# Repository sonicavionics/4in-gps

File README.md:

# GPS Module Repository

---

<div align="center">
  <div>

    <p><em>3D Render</em></p>
  </div>
  <br>

  <div>
    <br>
    <p><em>Schematic</em></p>
  </div>
  <br>
  
  <div>
    
    <br>
    <em>Footprint</em>
  </div>
</div>

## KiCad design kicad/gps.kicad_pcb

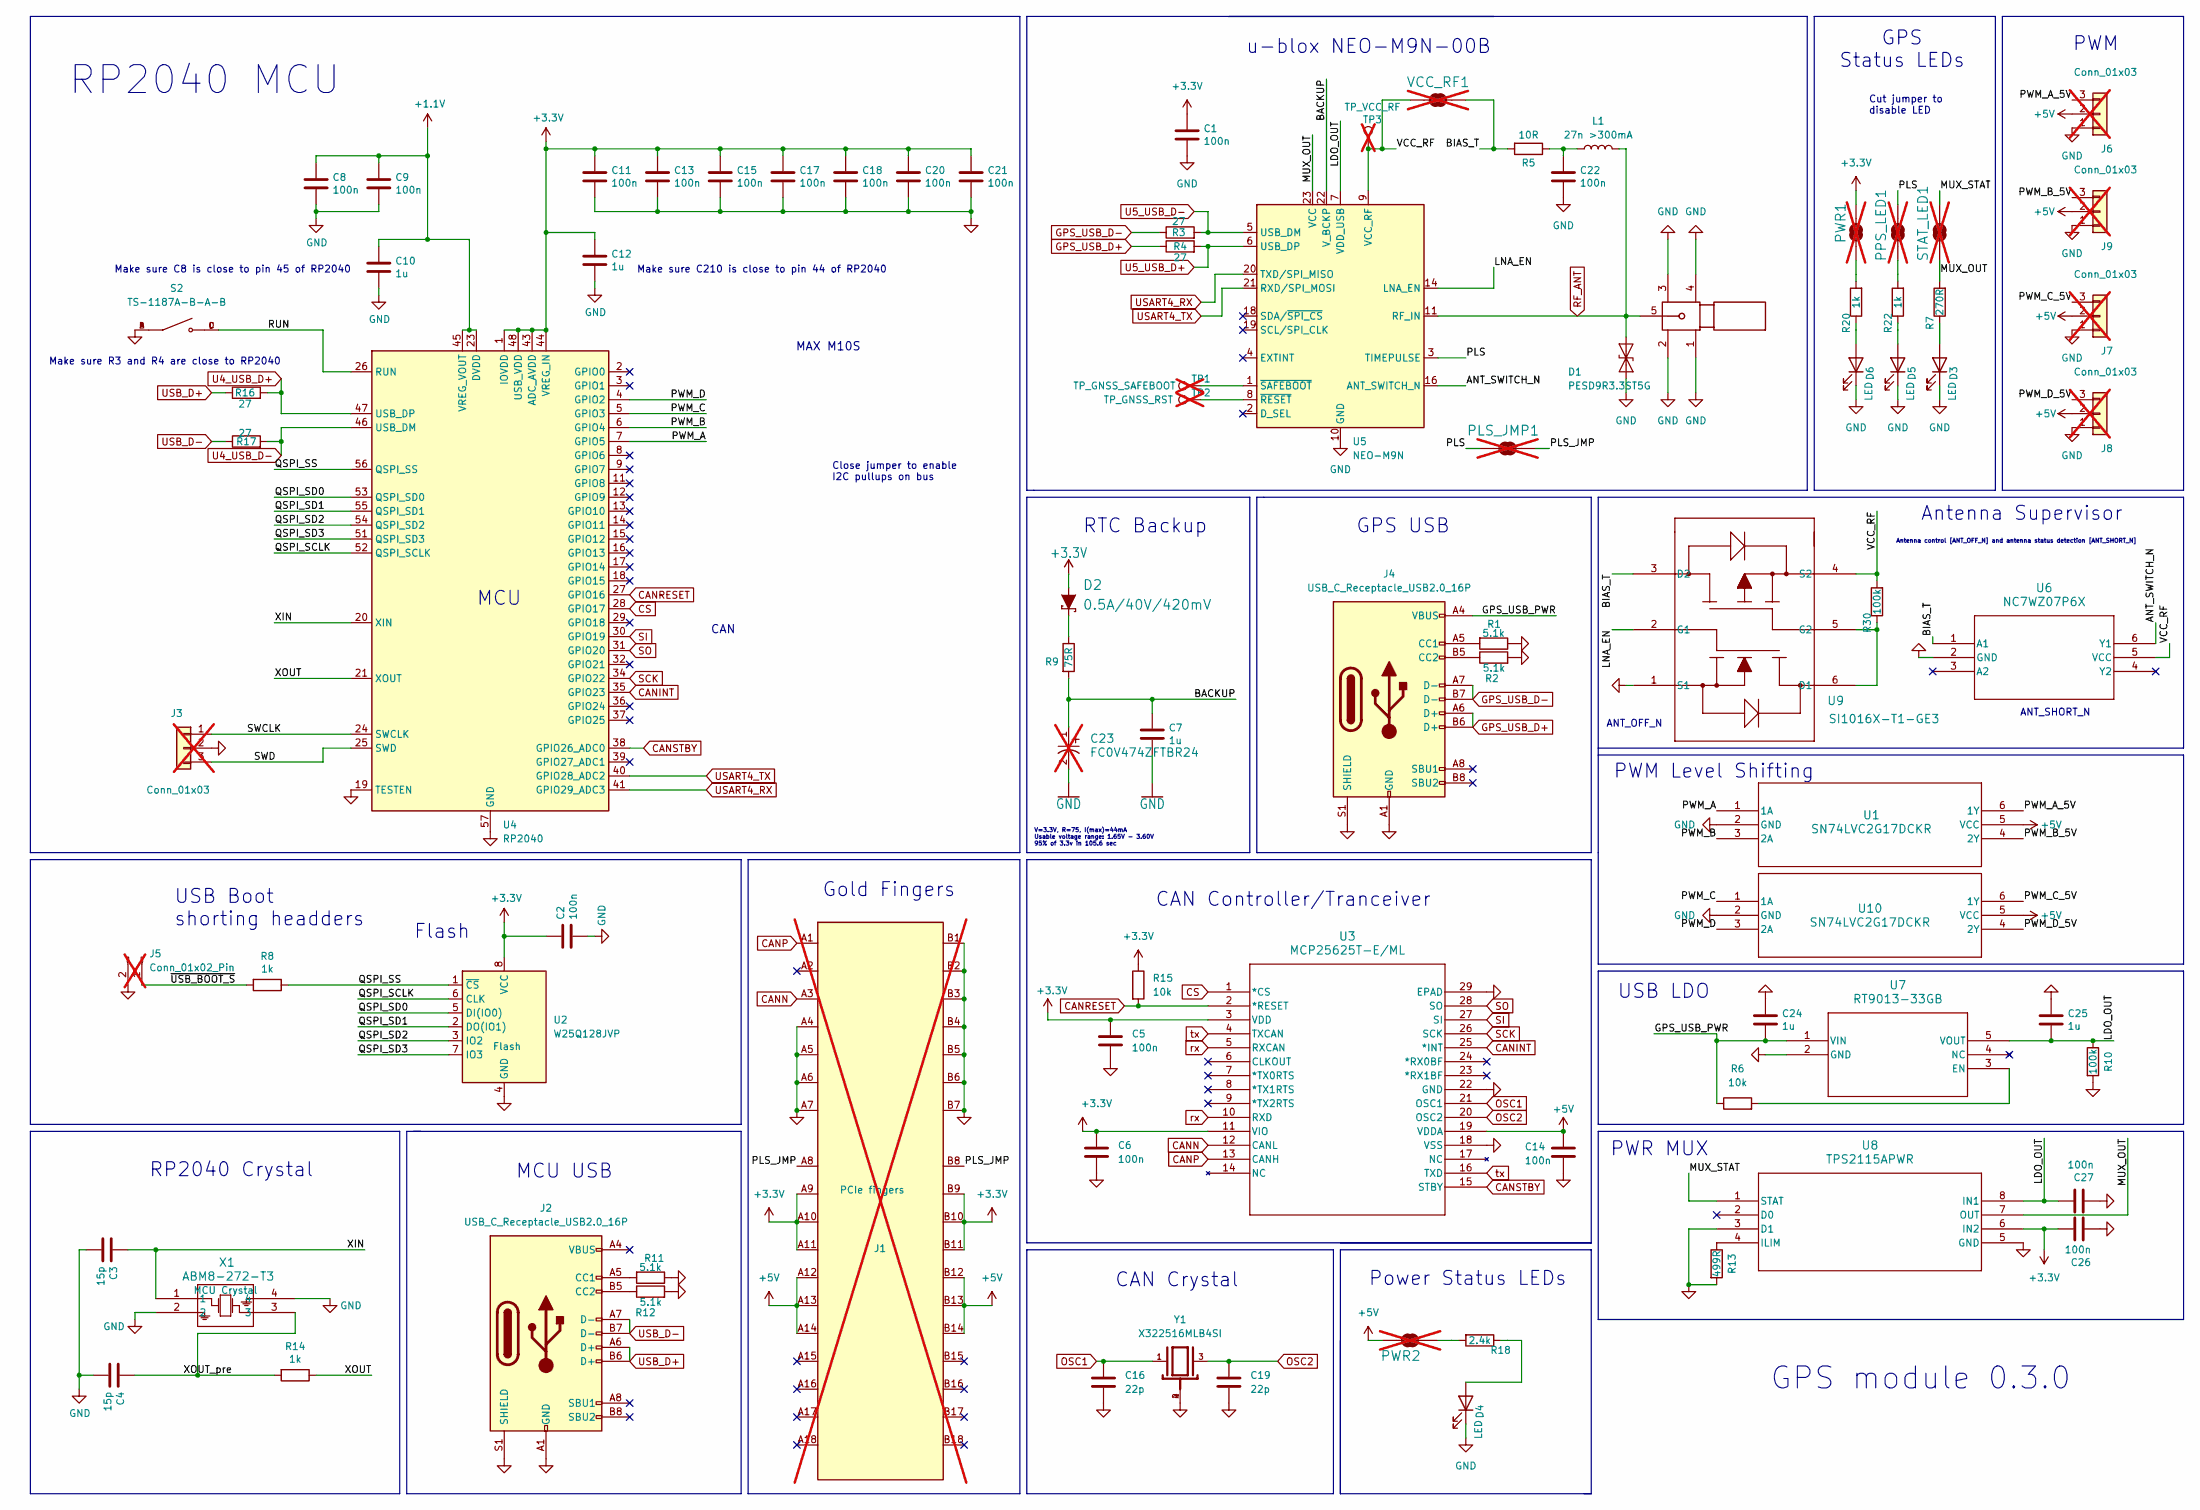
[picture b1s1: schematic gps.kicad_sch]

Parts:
C1, C2, C5, C6, C8, C9, C11, C13, C14, C15, C17, C18, C20, C21, C22, C26, C27: 100n; C_0402_1005Metric; LCSC Part # C307331
C3, C4: 15p; C_0402_1005Metric; LCSC Part # C1548
C7, C10, C12, C24, C25: 1u; C_0402_1005Metric; LCSC Part # C52923
C16, C19: 22p; C_0402_1005Metric; LCSC Part # C1555
C23: FC0V474ZFTBR24; FC0V474ZFTBR24_KEM; not fitted
D1: PESD9R3.3ST5G; D_SOD-923; LCSC C2912536
D2: 0.5A/40V/420mV; SOD-323; Manufacturer Part Number PMEGA4005EJ,115; LCSC Part # C426868
D3: LED; LED_0603_1608Metric; Manufacturer_Part_Number XL-1608UWC-04; LCSC Part # C965808
D4: LED; LED_0603_1608Metric; LCSC Part # C2286
D5: LED; LED_0603_1608Metric; Manufacturer_Part_Number KT-0603B; LCSC Part # C2288
D6: LED; LED_0603_1608Metric; Manufacturer_Part_Number KT-0603R; LCSC Part # C2286
J1: Bus_PCI_Express_x1; BUS_PCIexpress_x1; LCSC Part # n/a; not fitted
J2, J4: USB_C_Receptacle_USB2.0_16P; USB_C_Receptacle_Palconn_UTC16-G; LCSC Part # C2765186
J3: Conn_01x03; DEBUGHEADER; LCSC Part # n/a; not fitted
J5: Conn_01x02_Pin; SolderJumper-2_P1.3mm_Open_RoundedPad1.0x1.5mm; not fitted
J6, J7, J8, J9: Conn_01x03; PinHeader_1x03_P2.54mm_Vertical; LCSC Part # n/a; not fitted
L1: 27n >300mA; R_0402_1005Metric; Manufacturer Part Number LQG15HS27NJ02D; LCSC Part # C12669
PLS_JMP1: JUMPER-SMT_2_NC_TRACE_SILK; SolderJumper-2_P1.3mm_Open_RoundedPad1.0x1.5mm; not fitted
PPS_LED1: JUMPER-SMT_2_NC_TRACE_SILK; SMT-JUMPER_2_NC_TRACE_SILK; not fitted
PWR1, PWR2: JUMPER-SMT_2_NC_TRACE_SILK; SMT-JUMPER_2_NC_TRACE_SILK; not fitted
R1, R2, R11, R12: 5.1k; R_0402_1005Metric; LCSC Part # C25905
R3, R4, R16, R17: 27; R_0402_1005Metric; LCSC Part # C25100
R5: 10R; R_0402_1005Metric; Manufacturer Part Number 0402WGF100JTCE; LCSC Part # C25077
R6, R15: 10k; R_0402_1005Metric; LCSC Part # C25744
R7: 270R; R_0402_1005Metric; Manufacturer_Part_Number 0402WGF2700TCE; LCSC Part # C25099
R8, R14, R20, R22: 1k; R_0402_1005Metric; LCSC Part # C11702
R9: 75R; R_0805_2012Metric; Manufacturer_Part_Number 0805W8F750JT5E; LCSC Part # C17820
R10, R30: 100k; R_0402_1005Metric; Manufacturer Part Number 0402WGF1003TCE; LCSC Part # C25741
R13: 499R; R_0402_1005Metric; Manufacturer Part Number 0402WGF4990TCE; LCSC Part # C4125
R18: 2.4k; R_0402_1005Metric; Manufacturer_Part_Number 0402WGF2401TCE; LCSC Part # C25882
RF1: BWSMA-KWE-Z001; SMA-TH_BWSMA-KWE-Z001; Manufacturer Part Number BWSMA-KWE-Z001; LCSC Part # C496551
S2: TS-1187A-B-A-B; SW_TS-1187A-B-A-B; PARTREV A0; LCSC Part # C318884
STAT_LED1: JUMPER-SMT_2_NC_TRACE_SILK; SMT-JUMPER_2_NC_TRACE_SILK; not fitted
TP1: TP_GNSS_SAFEBOOT; TestPoint_Pad_D1.0mm; not fitted
TP2: TP_GNSS_RST; TestPoint_Pad_D1.0mm; not fitted
TP3: TP_VCC_RF; TestPoint_Pad_D1.0mm; not fitted
U1, U10: SN74LVC2G17DCKR; DCK6; MFR.Part # SN74LVC2G17DCKR; JLC Link JLCPCB Part
U2: W25Q128JVP; WSON-8-1EP_6x5mm_P1.27mm_EP3.4x4.3mm; LCSC C190862
U3: MCP25625T-E/ML; QFN28_6X6MC_MCH; LCSC Part # C191253
U4: RP2040; QFN-56-1EP_7x7mm_P0.4mm_EP3.2x3.2mm; LCSC C2040
U5: NEO-M9N; ublox_NEO
U6: NC7WZ07P6X; SC-88&slash_SC70-6&slash_SOT-363_419B-02_ONS; MFR.Part # NC7WZ07P6X; LCSC Part # C95342
U7: RT9013-33GB; SOT-23-5_RIT_LDO; MFR.Part # RT9013-33GB; LCSC Part # C47773
U8: TPS2115APWR; PW8
U9: SI1016X-T1-GE3; SOT_X-T1-GE3_VIS; Manufacturer Part Number SI1016X-T1-GE3; LCSC Part # C142570
VCC_RF1: JUMPER-SMT_2_NC_TRACE_SILK; SMT-JUMPER_2; not fitted
X1: ABM8-272-T3; ABM8-272-T3_ABR; LCSC Part # C20625731
Y1: X322516MLB4SI; OSC_X322516MLB4SI; PARTREV N/A; LCSC Part # C12668

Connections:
+1.1V: C8.1, C9.1, C10.1, U4.23 (DVDD), U4.45 (VREG_VOUT), U4.50 (DVDD)
+3.3V: C1.1, C2.1, C5.1, C6.1, C11.1, C12.1, C13.1, C15.1, C17.1, C18.1, C20.1, C21.1, C26.1, D2.A, J1.A9 (+3.3V), J1.A10 (+3.3V), J1.A11 (~PERST), J1.B9 (JTAG1), J1.B10 (3.3Vaux), J1.B11 (~WAKE), PWR1.2, R15.1, U2.8 (VCC), U3.3 (VDD), U3.11 (VIO), U4.1 (IOVDD), U4.10 (IOVDD), U4.22 (IOVDD), U4.33 (IOVDD), U4.42 (IOVDD), U4.43 (ADC_AVDD), U4.44 (VREG_IN), U4.48 (USB_VDD), U4.49 (IOVDD), U8.6 (IN2)
+5V: C14.1, J1.A12 (GND), J1.A13 (REFCLK+), J1.A14 (REFCLK-), J1.B12 (RSVD), J1.B13 (GND), J1.B14 (PETp0), J6.2, J7.2, J8.2, J9.2, PWR2.2, U1.5 (VCC), U3.19 (VDDA), U10.5 (VCC)
/ANT_SWITCH_N: U5.16 (ANT_SWITCH_N), U6.6 (Y1)
/BACKUP: C7.1, C23.1, R9.2, U5.22 (V_BCKP)
/BIAS_T: R5.2, U6.1 (A1), U9.3 (D2), VCC_RF1.1
/GPS_USB_PWR: C24.2, J4.A4 (VBUS), J4.A9 (VBUS), J4.B4 (VBUS), J4.B9 (VBUS), R6.1, U7.1 (VIN)
/LDO_OUT: C25.2, C27.1, R10.1, U5.7 (VDD_USB), U7.5 (VOUT), U8.8 (IN1)
/LNA_EN: U5.14 (LNA_EN), U9.2 (G1)
/MUX_OUT: R7.2, STAT_LED1.1, U5.23 (VCC), U8.7 (OUT)
/MUX_STAT: STAT_LED1.2, U8.1 (STAT)
/PLS: PLS_JMP1.2, PPS_LED1.2, U5.3 (TIMEPULSE); also elsewhere on the board
/PLS_JMP: J1.A8 (JTAG5), J1.B8 (+3.3V), PLS_JMP1.1; also elsewhere on the board
/PWM_A: U1.1 (1A), U4.7 (GPIO5)
/PWM_A_5V: J6.3, U1.6 (1Y)
/PWM_B: U1.3 (2A), U4.6 (GPIO4)
/PWM_B_5V: J9.3, U1.4 (2Y)
/PWM_C: U4.5 (GPIO3), U10.1 (1A)
/PWM_C_5V: J7.3, U10.6 (1Y)
/PWM_D: U4.4 (GPIO2), U10.3 (2A)
/PWM_D_5V: J8.3, U10.4 (2Y)
/QSPI_SCLK: U2.6 (CLK), U4.52 (QSPI_SCLK)
/QSPI_SD0: U2.5 (DI(IO0)), U4.53 (QSPI_SD0)
/QSPI_SD1: U2.2 (DO(IO1)), U4.55 (QSPI_SD1)
/QSPI_SD2: U2.3 (IO2), U4.54 (QSPI_SD2)
/QSPI_SD3: U2.7 (IO3), U4.51 (QSPI_SD3)
/QSPI_SS: R8.1, U2.1 (~CS), U4.56 (QSPI_SS)
/RUN: S2.C, S2.D, U4.26 (RUN)
/SWCLK: J3.1, U4.24 (SWCLK)
/SWD: J3.3, U4.25 (SWD)
/VCC_RF: R30.2, TP3.1, U5.9 (VCC_RF), U6.5 (VCC), U9.4 (S2), VCC_RF1.2
/XIN: C3.1, U4.20 (XIN), X1.1
/XOUT: R14.1, U4.21 (XOUT)
/XOUT_pre: C4.1, R14.2, X1.3
/~USB_BOOT_S: J5.1, R8.2
CANINT: U3.25 (*INT), U4.35 (GPIO23)
CANN: J1.A3 (+12V), U3.12 (CANL)
CANP: J1.A1 (~PRSNT1), U3.13 (CANH)
CANRESET: R15.2, U3.2 (*RESET), U4.27 (GPIO16)
CANSTBY: U3.15 (STBY), U4.38 (GPIO26_ADC0)
CS: U3.1 (*CS), U4.28 (GPIO17)
GND: C1.2, C2.2, C3.2, C4.2, C5.2, C6.2, C7.2, C8.2, C9.2, C10.2, C11.2, C12.2, C13.2, C14.2, C15.2, C16.2, C17.2, C18.2, C19.2, C20.2, C21.2, C22.2, C23.2, C24.1, C25.1, C26.2, C27.2, D1.1 (A1), D3.1 (K), D4.1 (K), D5.1 (K), D6.1 (K), J1.A4 (GND), J1.A5 (JTAG2), J1.A6 (JTAG3), J1.A7 (JTAG4), J1.B1 (+12V), J1.B2 (+12V), J1.B3 (+12V), J1.B4 (GND), J1.B5 (SMCLK), J1.B6 (SMDAT), J1.B7 (GND), J2.A1 (GND), J2.A12 (GND), J2.B1 (GND), J2.B12 (GND), J2.S1 (SHIELD), J3.2, J4.A1 (GND), J4.A12 (GND), J4.B1 (GND), J4.B12 (GND), J4.S1 (SHIELD), J5.2, J6.1, J7.1, J8.1, J9.1, R1.1, R2.2, R10.2, R11.1, R12.2, R13.2, RF1.1, RF1.2, RF1.3, RF1.4, S2.A, S2.B, U1.2 (GND), U2.4 (GND), U3.18 (VSS), U3.22 (GND), U3.29 (EPAD), U4.19 (TESTEN), U4.57 (GND), U5.10 (GND), U5.12 (GND), U5.13 (GND), U5.24 (GND), U6.2 (GND), U7.2 (GND), U8.3 (D1), U8.5 (GND), U9.1 (S1), U10.2 (GND), X1.2, X1.4, Y1.2, Y1.4
GPS_USB_D+: J4.A6 (D+), J4.B6 (D+), R4.1
GPS_USB_D-: J4.A7 (D-), J4.B7 (D-), R3.1
unnamed: C22.1, L1.1, R5.1
unnamed: D2.C, R9.1
unnamed: D3.2 (A), R7.1
unnamed: D4.2 (A), R18.1
unnamed: D5.2 (A), R22.1
unnamed: D6.2 (A), R20.1
unnamed: J2.A5 (CC1), R11.2
unnamed: J2.B5 (CC2), R12.1
unnamed: J4.A5 (CC1), R1.2
unnamed: J4.B5 (CC2), R2.1
unnamed: PPS_LED1.1, R22.2
unnamed: PWR1.1, R20.2
unnamed: PWR2.1, R18.2
unnamed: TP2.1, U5.8 (~RESET)
unnamed: TP1.1, U5.1 (~SAFEBOOT)
unnamed: R6.2, U7.3 (EN)
unnamed: R13.1, U8.4 (ILIM)
unnamed: R30.1, U9.5 (G2), U9.6 (D1)
OSC1: C16.1, U3.21 (OSC1), Y1.1
OSC2: C19.1, U3.20 (OSC2), Y1.3
RF_ANT: D1.2 (A2), L1.2, RF1.5, U5.11 (RF_IN)
SCK: U3.26 (SCK), U4.34 (GPIO22)
SI: U3.27 (SI), U4.30 (GPIO19)
SO: U3.28 (SO), U4.31 (GPIO20)
U4_USB_D+: R16.2, U4.47 (USB_DP)
U4_USB_D-: R17.2, U4.46 (USB_DM)
U5_USB_D+: R4.2, U5.6 (USB_DP)
U5_USB_D-: R3.2, U5.5 (USB_DM)
USART4_RX: U4.41 (GPIO29_ADC3), U5.20 (TXD/SPI_MISO)
USART4_TX: U4.40 (GPIO28_ADC2), U5.21 (RXD/SPI_MOSI)
USB_D+: J2.A6 (D+), J2.B6 (D+), R16.1
USB_D-: J2.A7 (D-), J2.B7 (D-), R17.1
rx: U3.5 (RXCAN), U3.10 (RXD)
tx: U3.4 (TXCAN), U3.16 (TXD)

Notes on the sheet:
Flash
CAN Crystal
GPS Status LEDs
CAN Controller/Tranceiver
Make sure R3 and R4 are close to RP2040
ANT_OFF_N
RP2040 MCU
Gold Fingers
GPS module 0.3.0
USB Boot shorting headders
u-blox NEO-M9N-00B
GPS USB
MCU
Antenna Supervisor
RTC Backup
PWM Level Shifting
Make sure C210 is close to pin 44 of RP2040
MAX M10S
MCU USB
Power Status LEDs
USB LDO
Cut jumper to disable LED
PWR MUX
ANT_SHORT_N
V=3.3V, R=75, I(max)=44mA Usable voltage range: 1.65V - 3.60V 95% of 3.3v in 105.6 sec
RP2040 Crystal
Antenna control [ANT_OFF_N] and antenna status detection [ANT_SHORT_N]
CAN
Make sure C8 is close to pin 45 of RP2040
Close jumper to enable I2C pullups on bus
PWM

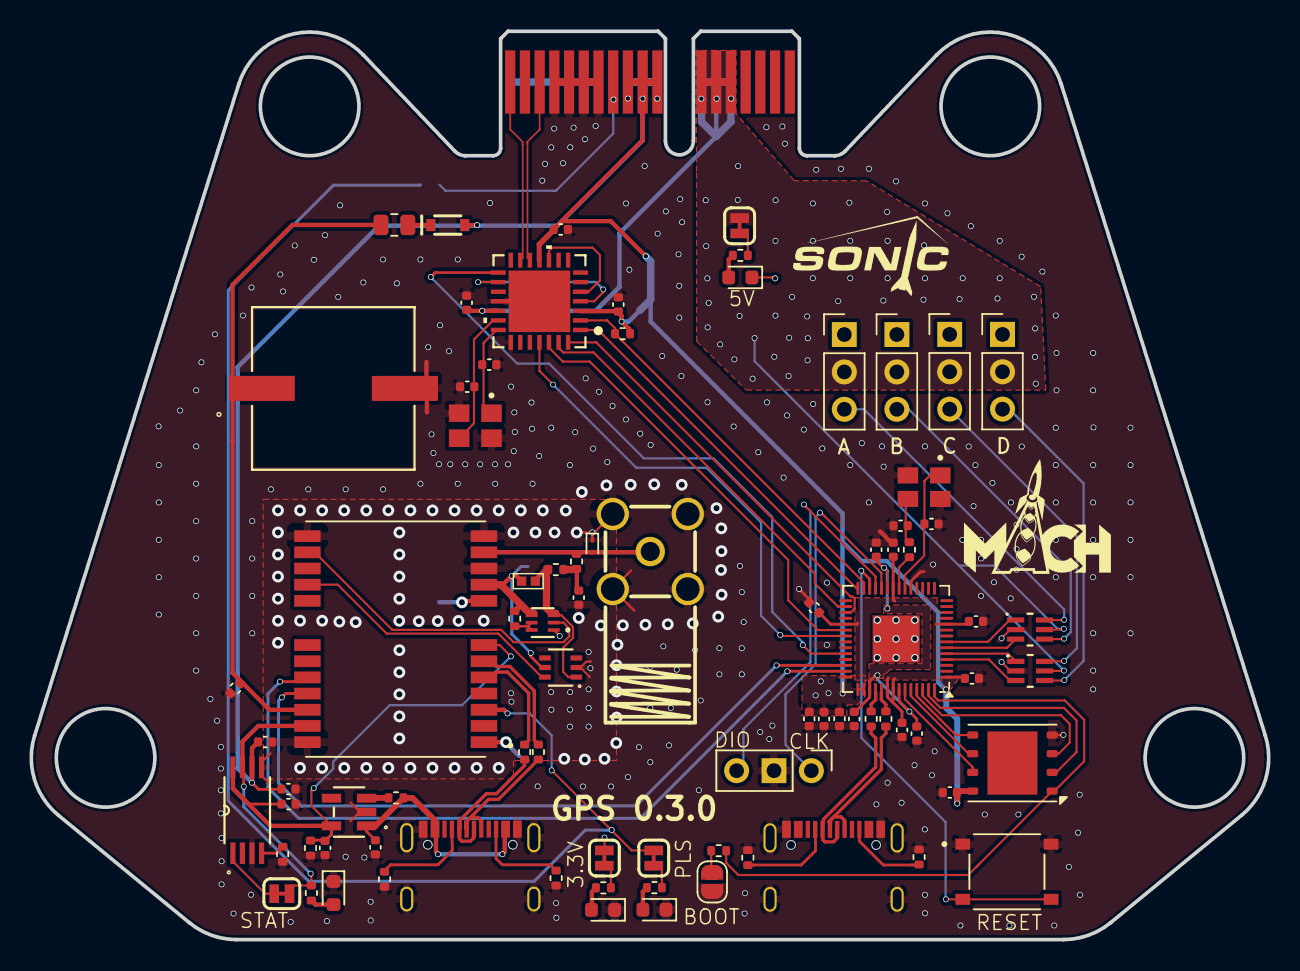
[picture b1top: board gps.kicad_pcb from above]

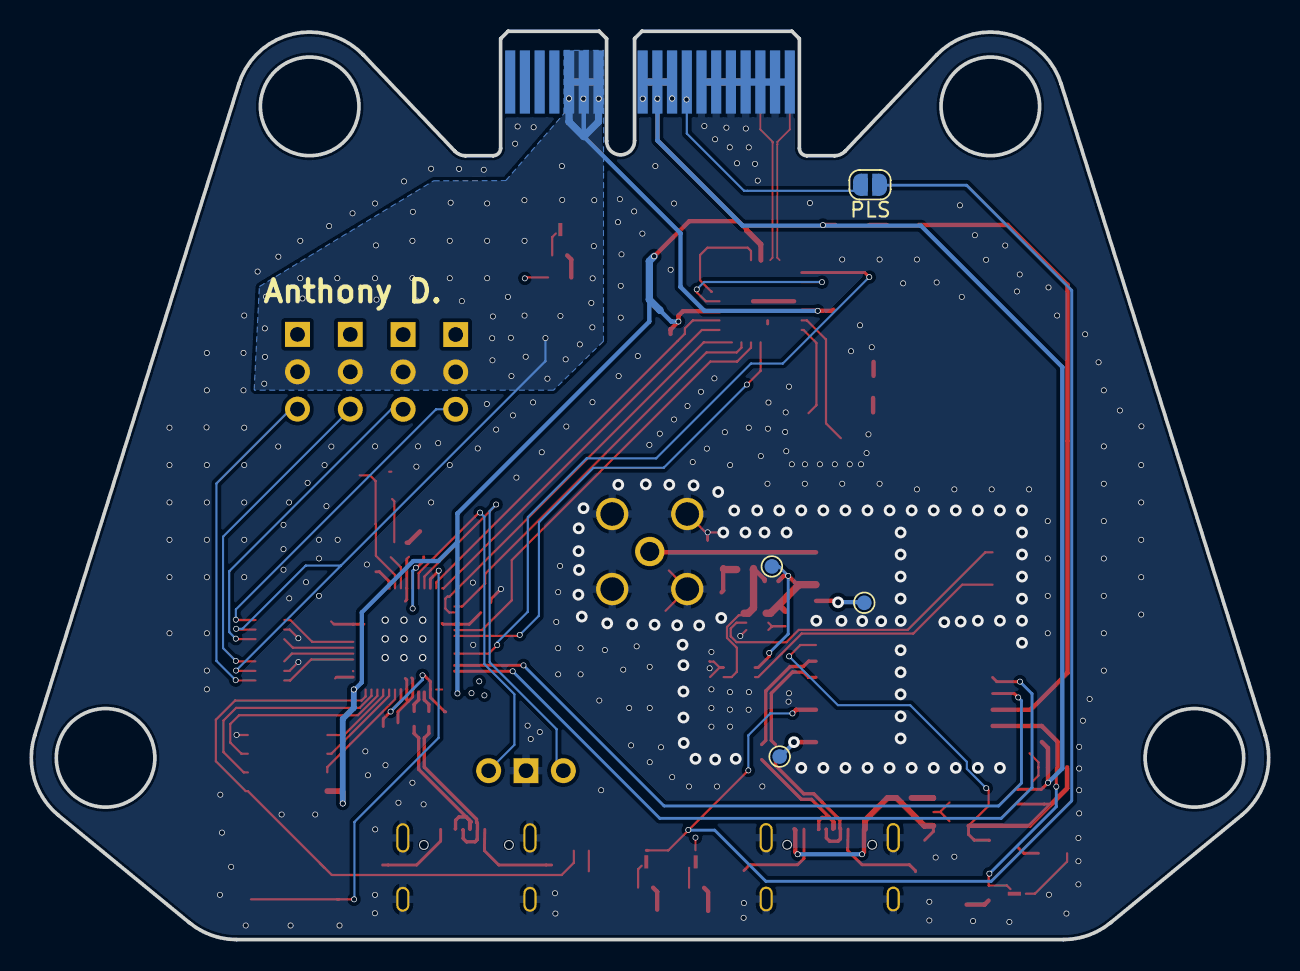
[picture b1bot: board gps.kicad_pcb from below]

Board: 4 copper layers, 84.1 x 61.7 mm, 88 parts (5 on the bottom side), 78 nets.

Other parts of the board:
PLS: JUMPER-SMT_2_NC_TRACE_SILK; SolderJumper-2_P1.3mm_Open_RoundedPad1.0x1.5mm
ballsack1: a5b3f77c-c1d0-4586-9ab7-7f2af37e3489

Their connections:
/PLS: PLS.2; also elsewhere on the board
/PLS_JMP: PLS.1; also elsewhere on the board

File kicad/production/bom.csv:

Designator,Footprint,Quantity,Value,LCSC Part #
BALLSACK1,a5b3f77c-c1d0-4586-9ab7-7f2af37e3489,1,,
"C1, C11, C13, C14, C15, C17, C18, C2, C20, C21, C22, C26, C27, C5, C6, C8, C9",0402,17,100n,C307331
"C10, C12, C24, C25, C7",0402,5,1u,C52923
"C16, C19",0402,2,22p,C1555
"C3, C4",0402,2,15p,C1548
D1,D_SOD-923,1,PESD9R3.3ST5G,C2912536
D2,SOD-323,1,0.5A/40V/420mV,C426868
D3,0603,1,LED,C965808
"D4, D6",0603,2,LED,C2286
D5,0603,1,LED,C2288
"J2, J4",USB_C_Receptacle_Palconn_UTC16-G,2,USB_C_Receptacle_USB2.0_16P,C2765186
L1,0402,1,27n >300mA,C12669
"R1, R11, R12, R2",0402,4,5.1k,C25905
"R10, R30",0402,2,100k,C25741
R13,0402,1,499R,C4125
"R14, R20, R22, R8",0402,4,1k,C11702
"R15, R6",0402,2,10k,C25744
"R16, R17, R3, R4",0402,4,27,C25100
R18,0402,1,2.4k,C25882
R5,0402,1,10R,C25077
R7,0402,1,270R,C25099
R9,0805,1,75R,C17820
RF1,SMA-TH_BWSMA-KWE-Z001,1,BWSMA-KWE-Z001,C496551
S2,SW_TS-1187A-B-A-B,1,TS-1187A-B-A-B,C318884
"U1, U10",DCK6,2,SN74LVC2G17DCKR,C50714
U2,WSON-8-1EP_6x5mm_P1.27mm_EP3.4x4.3mm,1,W25Q128JVP,C190862
U3,QFN28_6X6MC_MCH,1,MCP25625T-E/ML,C191253
U4,QFN-56-1EP_7x7mm_P0.4mm_EP3.2x3.2mm,1,RP2040,C2040
U5,XCVR_NEO-M9N-00B,1,NEO-M9N,
U6,SC-88&slash_SC70-6&slash_SOT-363_419B-02_ONS,1,NC7WZ07P6X,C95342
U7,SOT-23-5_RIT_LDO,1,RT9013-33GB,C47773
U8,PW8,1,TPS2115APWR,
U9,SOT_X-T1-GE3_VIS,1,SI1016X-T1-GE3,C142570
X1,ABM8-272-T3_ABR,1,ABM8-272-T3,C20625731
Y1,OSC_X322516MLB4SI,1,X322516MLB4SI,C12668

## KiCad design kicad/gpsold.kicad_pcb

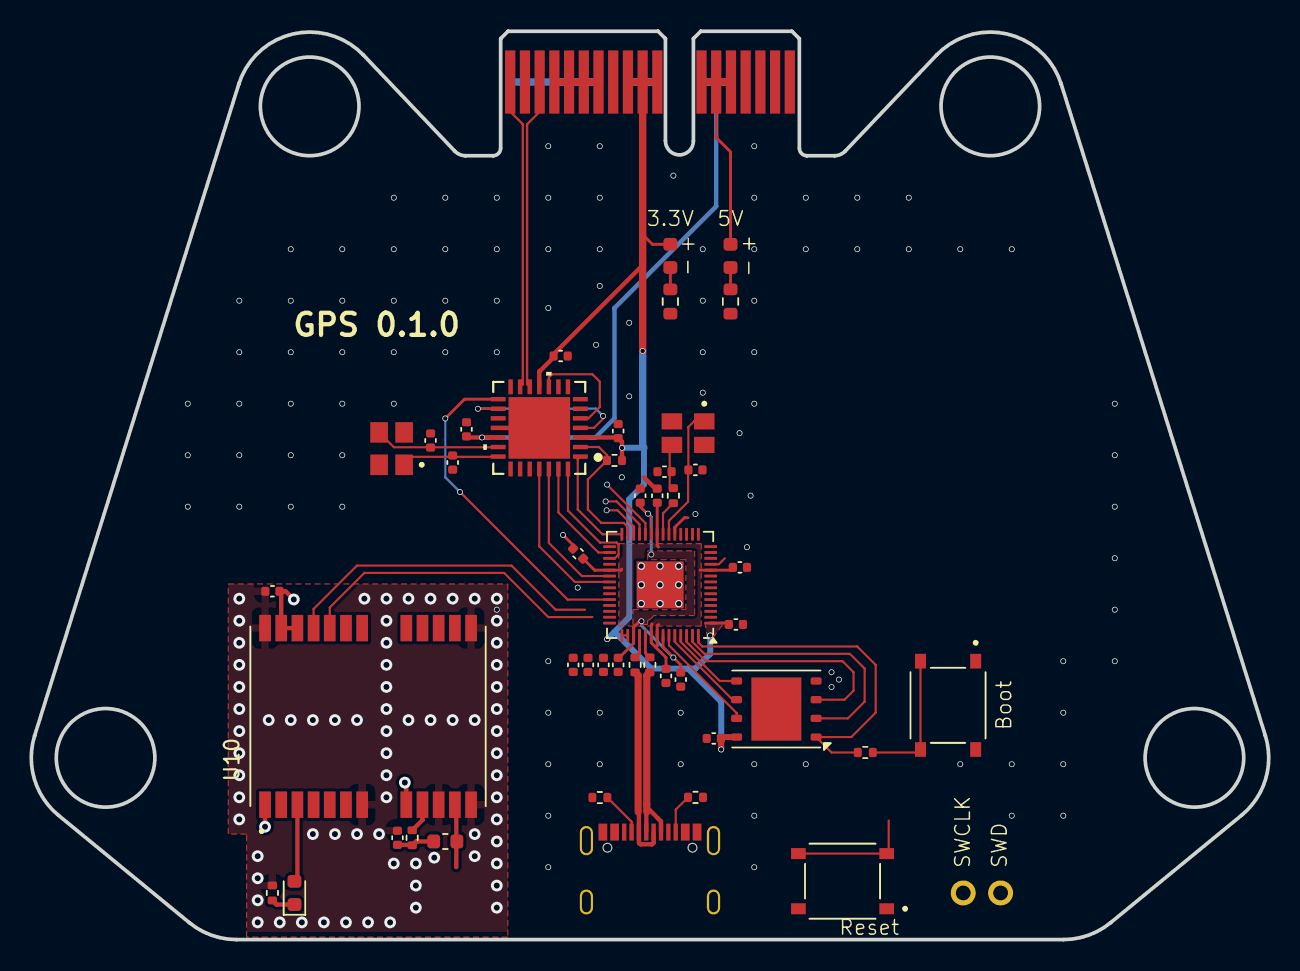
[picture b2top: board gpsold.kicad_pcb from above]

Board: 2 copper layers, 84.1 x 61.7 mm, 47 parts (1 on the bottom side), 38 nets.

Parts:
C10, C11: 15p; C_0402_1005Metric
C32: 100n 10% 16V X7R; C_0402_1005Metric
C33, C40, C90, C92, C93, C206, C207, C209, C211, C212, C213, C214, C215, C216: 100n; C_0402_1005Metric
C94, C95: 22p; C_0402_1005Metric
C208, C210: 1u; C_0402_1005Metric
D1, D2: LED; LED_0603_1608Metric
D2#2: BLUE; LED_0603_1608Metric
J1: Bus_PCI_Express_x1; BUS_PCIexpress_x1
J4: Conn_01x02; PinHeader_1x02_P2.54mm_Vertical
J6: USB_C_Receptacle_USB2.0_16P; USB_C_Receptacle_Palconn_UTC16-G
L5: 27n >300mA; L_0603_1608Metric
R1, R2: 150; R_0603_1608Metric
R3: 10R; R_0402_1005Metric
R3#2, R4#2: 5.1k; R_0402_1005Metric
R4, R12, R30: 1k; R_0402_1005Metric
R91: 10k; R_0402_1005Metric
R203, R204: 27; R_0402_1005Metric
S1, S2: TS-1187A-B-A-B; SW_TS-1187A-B-A-B
U2: RP2040; QFN-56-1EP_7x7mm_P0.4mm_EP3.2x3.2mm
U4: W25Q128JVP; WSON-8-1EP_6x5mm_P1.27mm_EP3.4x4.3mm
U9: MCP25625T-E/ML; QFN28_6X6MC_MCH
U10: NEO-M9N; XCVR_NEO-M9N-00B
X1: ABM8-272-T3; ABM8-272-T3_ABR
Y2: X322516MLB4SI; OSC_X322516MLB4SI

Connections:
+1.1V: C206.1, C207.1, C208.1, U2.23 (DVDD), U2.45 (VREG_VOUT), U2.50 (DVDD)
+3.3V: C40.1, C90.1, C92.1, C209.1, C210.1, C211.1, C212.1, C213.1, C214.1, C215.1, C216.1, D1.2 (A), J1.A9 (+3.3V), J1.A10 (+3.3V), J1.A11 (~PERST), J1.B9 (JTAG1), J1.B10 (3.3Vaux), J1.B11 (~WAKE), R91.1, U2.1 (IOVDD), U2.10 (IOVDD), U2.22 (IOVDD), U2.33 (IOVDD), U2.42 (IOVDD), U2.43 (ADC_AVDD), U2.44 (VREG_IN), U2.48 (USB_VDD), U2.49 (IOVDD), U4.8 (VCC), U9.3 (VDD), U9.11 (VIO)
+5V: C93.1, D2.2 (A), J1.A12 (GND), J1.A13 (REFCLK+), J1.A14 (REFCLK-), J1.B12 (RSVD), J1.B13 (GND), J1.B14 (PETp0), U9.19 (VDDA)
/QSPI_SCLK: U2.52 (QSPI_SCLK), U4.6 (CLK)
/QSPI_SD0: U2.53 (QSPI_SD0), U4.5 (DI(IO0))
/QSPI_SD1: U2.55 (QSPI_SD1), U4.2 (DO(IO1))
/QSPI_SD2: U2.54 (QSPI_SD2), U4.3 (IO2)
/QSPI_SD3: U2.51 (QSPI_SD3), U4.7 (IO3)
/QSPI_SS: R30.1, U2.56 (QSPI_SS), U4.1 (~CS)
/RUN: S2.C, S2.D, U2.26 (RUN)
/SWCLK: J4.1, U2.24 (SWCLK)
/SWD: J4.2, U2.25 (SWD)
/USB_D2+: R203.2, U2.47 (USB_DP)
/USB_D2-: R204.2, U2.46 (USB_DM)
/XIN: C10.1, U2.20 (XIN), X1.1
/XOUT: R12.1, U2.21 (XOUT)
/XOUT_pre: C11.1, R12.2, X1.3
/~USB_BOOT_S: R30.2, S1.C, S1.D
CANINT: U2.35 (GPIO23), U9.25 (*INT)
CANN: J1.A3 (+12V), U9.12 (CANL)
CANP: J1.A1 (~PRSNT1), U9.13 (CANH)
CANRESET: R91.2, U2.27 (GPIO16), U9.2 (*RESET)
CANSTBY: U2.38 (GPIO26_ADC0), U9.15 (STBY)
CS: U2.28 (GPIO17), U9.1 (*CS)
GND: C10.2, C11.2, C32.2, C33.2, C40.2, C90.2, C92.2, C93.2, C94.2, C95.2, C206.2, C207.2, C208.2, C209.2, C210.2, C211.2, C212.2, C213.2, C214.2, C215.2, C216.2, J1.A4 (GND), J1.A5 (JTAG2), J1.A6 (JTAG3), J1.A7 (JTAG4), J1.B1 (+12V), J1.B2 (+12V), J1.B3 (+12V), J1.B4 (GND), J1.B5 (SMCLK), J1.B6 (SMDAT), J1.B7 (GND), J6.A1 (GND), J6.A12 (GND), J6.B1 (GND), J6.B12 (GND), J6.S1 (SHIELD), R1.2, R2.2, R3#2.2, R4.2, R4#2.1, S1.A, S1.B, S2.A, S2.B, U2.19 (TESTEN), U2.57 (GND), U4.4 (GND), U9.18 (VSS), U9.22 (GND), U9.29 (EPAD), U10.7 (VDD_USB), U10.10 (GND), U10.12 (GND), U10.13 (GND), U10.24 (GND), X1.2, X1.4, Y2.2, Y2.4
unnamed: D1.1 (K), R1.1
unnamed: D2.1 (K), D2#2.1 (K), R2.1, R4.1
unnamed: J6.A5 (CC1), R4#2.2
unnamed: J6.B5 (CC2), R3#2.1
OSC1: C94.1, U9.21 (OSC1), Y2.1
OSC2: C95.1, U9.20 (OSC2), Y2.3
SCK: U2.34 (GPIO22), U9.26 (SCK)
SI: U2.30 (GPIO19), U9.27 (SI)
SO: U2.31 (GPIO20), U9.28 (SO)
USB_D+: J6.A6 (D+), J6.B6 (D+), R203.1
USB_D-: J6.A7 (D-), J6.B7 (D-), R204.1
rx: U9.5 (RXCAN), U9.10 (RXD)
tx: U9.4 (TXCAN), U9.16 (TXD)

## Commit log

2025-01-24 Initial commit: M10S PCB design
    Created the initial PCB design for the M10S module. Used template files from the 4in-sensors KiCad repository as a starting point for the layout and design. Adjusted components and schematics to fit 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
2025-01-24 Renamed gps folder to kicad
2025-01-24 Auto-exported schematic, PCB, and 3D model
2025-01-24 Update schematic: added power and function LEDs for GPS
2025-01-25 Switch from MAX M10S to NEO-M9N for enhanced GPS performance
    Switched from MAX M10S to NEO-M9N for improved GPS preformance. The NEO-M9N offers faster position acquisition with concurrent GNSS support (GPS, Galileo, GLONASS, BeiDou), higher accuracy, and up to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
2025-01-26 Delete kicad/New CATIA Drawing.CATDrawing
    Deleted an unintended file that was mistakenly added to the repository.
2025-01-26 Update images
2025-02-03 Add USB hub
2025-02-03 update pcb
2025-02-03 Remove outdated file gpsold
2025-02-15 Update footprints
2025-02-15 Add CAD for antenna
2025-02-15 Update antenna position
2025-03-07 Update antenna
2025-03-07 Remove temporary files
2025-03-07 add board.step to solidworks folder
2025-03-07 create inital gps board assembly
2025-03-07 make antenna 90 degrees
2025-03-07 increase to 7 modules
2025-03-07 add **/~ to .gitignore
2025-03-07 rotate antenna
2025-03-08 export step file
2025-03-08 rename step to gps.step
2025-03-09 update assemblies
2025-03-25 update Antenna.SLDASM file
2025-05-04 Add MOSFET bias-tee switch for active GPS antenna
2025-05-04 Finish GPS routing and LNA control
    - Added LNA_EN switch circuit with IRLML6344
    - Finalized VCC_RF routing and return path
    - Cleaned up UART1 connection on GPIO28/29
2025-05-04 Update all component properites
2025-05-04 Organize Schematic
2025-05-06 remove *.kicad_prl and add to gitignore
2025-05-19 Fix MCU Ground Pour
2025-05-19 Fix DRC Violations
2025-05-19 Via Stitch
2025-05-25 Add TVS Diode
2025-05-25 Add TVS Diode to footprint
2025-05-25 Update gate resistor value and apply general BOM improvements
    - Changed gate resistor R6 from 10kΩ to 2.2kΩ to improve MOSFET switching speed while maintaining safe drive current for LNA_EN pin.
    - Updated associated resistor part to a 0402 UNI-ROYAL 2.2kΩ variant with high stock from JLCPCB.
    - Refined BOM fields for several components including RF connector (RF1) and battery holder (BAT1) to match R5 formatting.
    - Ensured consistent metadata across all key parts: datasheets, LCSC part numbers, and manufacturer info.
2025-05-25 Update LED Positions
    Move LEDs to the front of the board for 3.3V and 5V power
2025-05-25 Move Gps Silkscreen to Front of Board
2025-05-25 update rack outline dxf
2025-05-25 Fix Battery Position
2025-06-07 Update components for order
2025-06-07 Move Boot pins
2025-06-07 Fix Usb Position
2025-06-07 Generate Fabrication Files
2025-06-07 Final Commit before 0.2.0 Order
2025-06-21 Add USB detection
2025-07-23 Big Fixes
2025-07-23 Add Supercap
2025-07-23 Major updates
2025-07-23 UPDATES
    - Updated antenna short-circuit monitor in accordance with MAX-M10S documentation
    - Added LDO from USB power to address issue where NEO-M9N did not recognize USB connection
    - Implemented power multiplexer prioritizing USB LDO; board can now be powered via USB, battery, or PowerSim
    - If USB is not connected, power negotiation defaults to the 3.3V board rail
    - Added VCC_RF bypass option allowing direct connection to Bias-T
    *Add test points
2025-07-23 Major Fixes
    Fixed impedances in accordance to JLC04161H-7628 Stackup
    Implemented footprinting for all components mentioned in last commit
    minor schematic tweaks and additions
2025-07-23 Add Bypasses
2025-07-24 Add Servo Outputs
2025-07-24 Fixed Stackup
2025-07-24 Add Power Zone for Servos
2025-07-24 Production File Generation
